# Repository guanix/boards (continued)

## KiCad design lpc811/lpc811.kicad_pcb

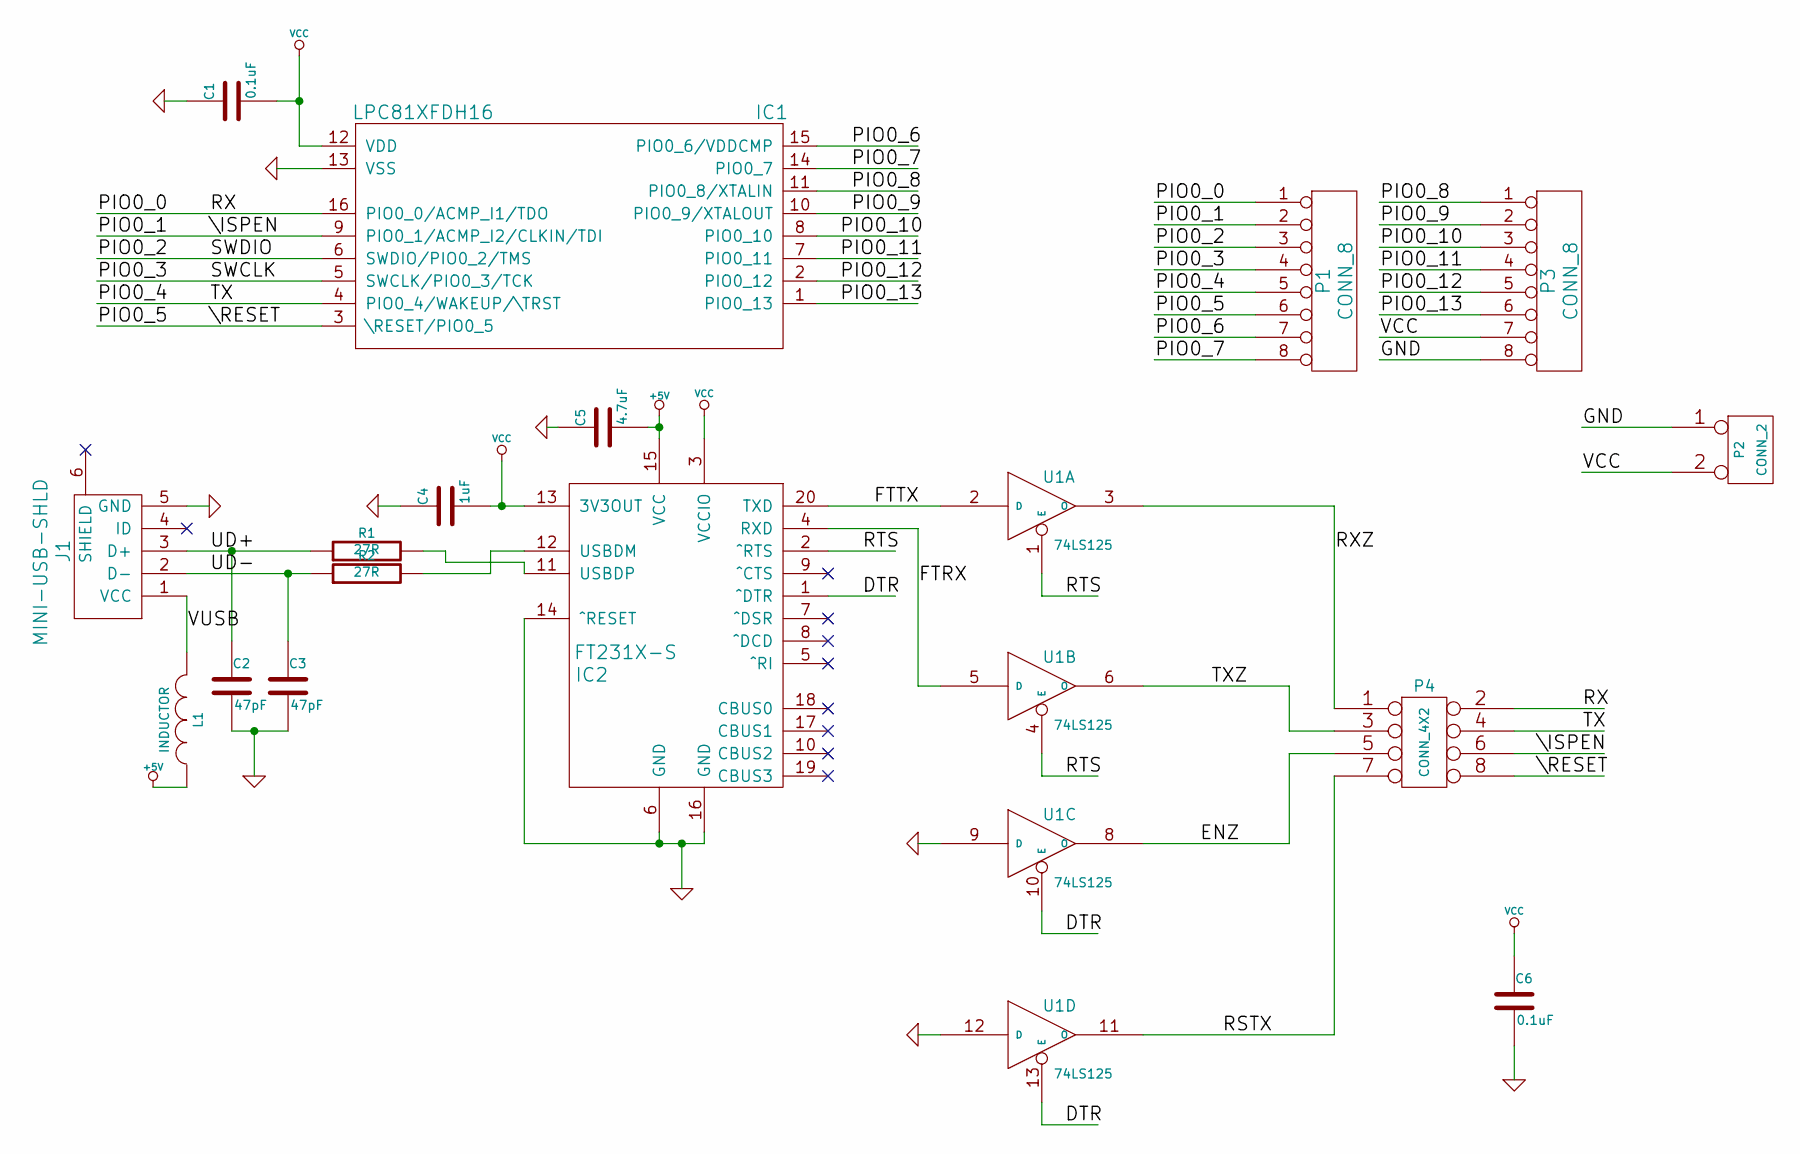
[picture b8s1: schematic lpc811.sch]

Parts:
C1, C6: 0.1uF
C2, C3: 47pF
C4: 1uF
C5: 4.7uF
IC1: LPC81XFDH16
IC2: FT231X-S
J1: MINI-USB-SHLD
L1: INDUCTOR
P1, P3: CONN_8
P2: CONN_2
P4: CONN_4X2
R1, R2: 27R
U1: 74LS125

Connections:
+5V: C5.2, IC2.15 (VCC), L1.1
/DTR: IC2.1 (^DTR), U1.10 (E), U1.13 (E)
/ENZ: P4.5, U1.8 (O)
/FTRX: IC2.4 (RXD), U1.5 (D)
/FTTX: IC2.20 (TXD), U1.2 (D)
/PIO0_0: IC1.16 (PIO0_0/ACMP_I1/TDO), P1.1, P4.2
/PIO0_1: IC1.9 (PIO0_1/ACMP_I2/CLKIN/TDI), P1.2, P4.6
/PIO0_2: IC1.6 (SWDIO/PIO0_2/TMS), P1.3
/PIO0_3: IC1.5 (SWCLK/PIO0_3/TCK), P1.4
/PIO0_4: IC1.4 (PIO0_4/WAKEUP/\TRST), P1.5, P4.4
/PIO0_5: IC1.3 (\RESET/PIO0_5), P1.6, P4.8
/PIO0_6: IC1.15 (PIO0_6/VDDCMP), P1.7
/PIO0_7: IC1.14 (PIO0_7), P1.8
/PIO0_8: IC1.11 (PIO0_8/XTALIN), P3.1
/PIO0_9: IC1.10 (PIO0_9/XTALOUT), P3.2
/PIO0_10: IC1.8 (PIO0_10), P3.3
/PIO0_11: IC1.7 (PIO0_11), P3.4
/PIO0_12: IC1.2 (PIO0_12), P3.5
/PIO0_13: IC1.1 (PIO0_13), P3.6
/RSTX: P4.7, U1.11 (O)
/RTS: IC2.2 (^RTS), U1.1 (E), U1.4 (E)
/RXZ: P4.1, U1.3 (O)
/TXZ: P4.3, U1.6 (O)
/UD+: C2.1, J1.3 (D+), R1.1
/UD-: C3.1, J1.2 (D-), R2.1
/VUSB: J1.1 (VCC), L1.2
GND: C1.1, C2.2, C3.2, C4.1, C5.1, C6.2, IC1.13 (VSS), IC2.6 (GND), IC2.14 (^RESET), IC2.16 (GND), J1.5 (GND), P2.1, P3.8, U1.7 (GND), U1.9 (D), U1.12 (D)
unnamed: IC2.11 (USBDP), R1.2
unnamed: IC2.12 (USBDM), R2.2
VCC: C1.2, C4.2, C6.1, IC1.12 (VDD), IC2.3 (VCCIO), IC2.13 (3V3OUT), P2.2 (PM), P3.7, U1.14 (VCC)

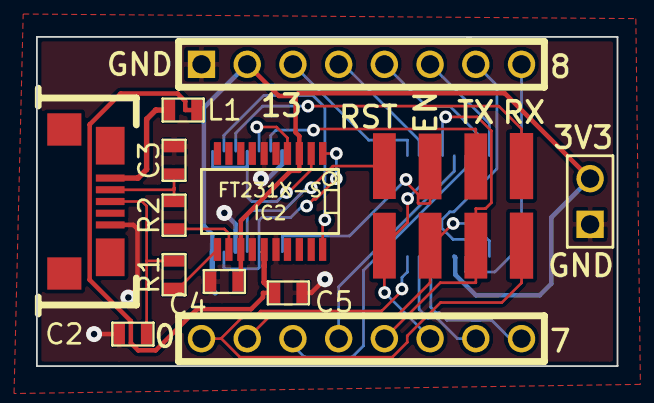
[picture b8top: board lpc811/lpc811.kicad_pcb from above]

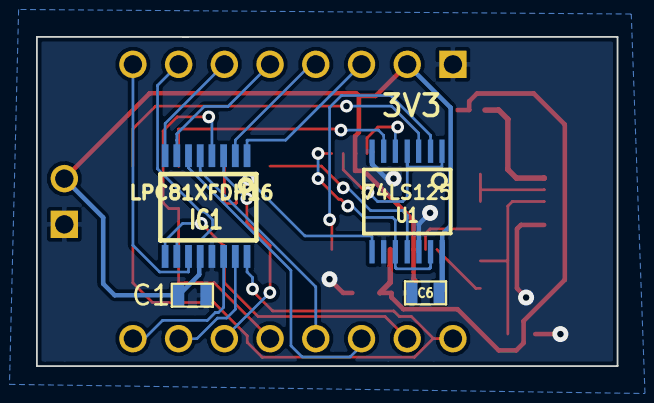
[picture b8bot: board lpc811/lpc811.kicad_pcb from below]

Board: 2 copper layers, 32.3 x 18.3 mm, 17 parts (4 on the bottom side), 30 nets.

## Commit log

2013-01-28 cam85: ATtiny85 based shutter timer for keychain spy cameras
2013-01-28 proximity: nRF51822 based Bluetooth Low Energy proximity tag and breakout board
2013-01-28 caissie: Infrared LED array with Infineon LED drivers
2013-01-28 shoe: 16 LED controller board with ATmega328P and TLC5940
2013-01-28 gitignore
2013-01-28 Joule thief
2013-01-28 smallled: Breakout board for single 0603 LED
2013-01-28 ft231x: FTDI FT231X breakout board
2013-01-28 ds3930bo
2013-01-30 PWM version of lamp module
2013-01-30 Joulethief library cache
2013-01-30 Proximity tag routing done
2013-01-30 More changes for DFM
2013-02-01 Minor changes
2013-02-06 library module and dcm files
2013-02-06 LTC3105 breakout board
2013-02-07 LTC3105 breakout board based on potentiometers
2013-02-08 LTC3588 energy harvesting breakout board
2013-02-09 Redesign for optocouplers
2013-02-13 cleanup
2013-02-13 readme
2013-02-15 Linear Technology energy harvesting ICs
2013-02-15 gitignore update
2013-02-15 lamppwm board updates
2013-02-15 Joule thief larger pads
2013-02-15 LTC3588 breakout board updates
2013-02-15 LTC3105 breakout board updates
2013-02-15 LTC3108 breakout board
2013-02-15 Board for WS2811 RGB module (actually WS2812)
2013-02-20 Clerical updates
2013-02-20 Update library paths
2013-02-20 Library updates
2013-02-20 Brain Bats power
2013-02-20 LPC1114FN28 LPC1114 programmer
2013-02-20 nRF51822 proximity tag pre-balun
2013-02-20 RFM12B transceiver breakout board
2013-02-20 Watering system master
2013-02-20 Audio interface for radios
2013-02-20 ATtiny85 infrared board
2013-02-20 updated gitignore
2013-02-20 more gitignore
2013-02-20 KiCad documentation library
2013-02-20 Original Brain Bats rewards module
2013-02-20 TSSOP breakout
2013-02-20 Watering system slave
2013-02-20 Watering system slave 2
2013-02-21 Shoe board v2
    - Add PTC fuse and reverse protection shunt diode
    - Replace IR section (because of timer conflict) with exposed serial
2013-02-21 Complete silkscreen
2013-02-21 IR slave board for shoe
2013-02-21 Shoe IR board updates
2013-02-21 MAX1555 breakout board
2013-02-21 shoe updates
2013-02-21 schematic temporary files in gitignor
2013-02-21 Brain Bats PWM updates
2013-02-22 LTC3783 high power LED driver breakout board, incomplete
2013-02-22 Library changes
2013-02-22 MAX1555 update
2013-02-28 TLC551 timer based Joule thief
2013-02-28 Surface mount Joule thief
2013-02-28 Cree based Joule thief
2013-03-01 Simple ATtiny85 based PWM LED dimmer
2013-03-04 lamppwm updates
2013-03-04 cam85 updates
2013-03-04 Final dimmer layout
2013-03-04 remove guan.bck
2013-03-04 Original Joule thief tweak
2013-03-04 Joule thief TLC551 timer update
2013-03-04 PCB capacitive button test board
2013-03-04 Captest silkscreen adjustments
2013-03-04 Captest updates
    * Change to SOIC-20 version of ATtiny861
    * Add filtering caps on sense pins
2013-03-04 Footprint: SOIC-20 8mm
2013-03-05 ATtiny10 SOT23-6 breakout board
2013-03-05 Captest update with TSSOP and more density
2013-03-05 Optimize captest layout
2013-03-05 4.5mm wide TSSOP-20 for ATtiny261
2013-03-07 Correct WS2811 (WS2812) footprint
2013-03-07 updated footprint for ws2811/ws2812
2013-03-11 Better routing of ground pour around ATtiny861 main bypass cap
2013-03-24 Cicada tracker
2013-04-21 Label updates
2013-04-22 nRF51822 proximity tag updates: - Ordinary crystal instead of CMOS oscillator - Regular pin header for SWDIO and SWCLK
2013-04-22 cicada updates
2013-04-22 Data logger first attempt
2013-04-22 Color Life vertex
2013-04-22 LTC3783
2013-04-22 Symbol and footprint library updates
2013-04-22 Color Life edge board
2013-04-22 proximity board updates
2013-04-27 ADC based capacitive touch test board, ATtiny861A
2013-04-27 Capacitive test button
2013-05-01 ATxmega16A4U breakout board
2013-05-02 OLED name tag and JST-PH-2 footprint
2013-05-03 Game of Life vertex board rev1
2013-05-04 module changes
2013-05-04 edge boards
2013-05-05 Last version before ATtiny24A
2013-05-06 ATtiny24A based edge board
2013-05-07 ATxmega16A4U updates
2013-05-07 nametag
2013-05-07 schematic symbols
2013-05-07 ws2811 changes
2013-05-09 BL600 BLE nRF51822 module breakout board
2013-05-10 Game of Life edge board rerouting
2013-05-10 BL600 add ARM 10/9 pin SWD header
2013-05-10 proximity tag updates
2013-05-10 vertex board game of life updates
2013-05-10 LPC811 board take 1
2013-05-10 LPC811 board take 2
2013-05-11 SOIC-14 update
2013-05-16 Only one cap button, add LED to Game of Life edge boards
2013-05-16 Vertex board updates
2013-05-16 Connect CR2032 holder directly to 3V3
2013-05-21 module updates
2013-05-21 Proximity tag version 2
2013-10-07 Hack Manhattan Color Life boards final version
2013-10-07 nRF24L01+ button for Hall of Science
2013-10-07 Erroneous file
2013-10-08 Creative Commons Attribution 3.0 Unported License
2013-10-13 Wireless thermostat/boiler controller
